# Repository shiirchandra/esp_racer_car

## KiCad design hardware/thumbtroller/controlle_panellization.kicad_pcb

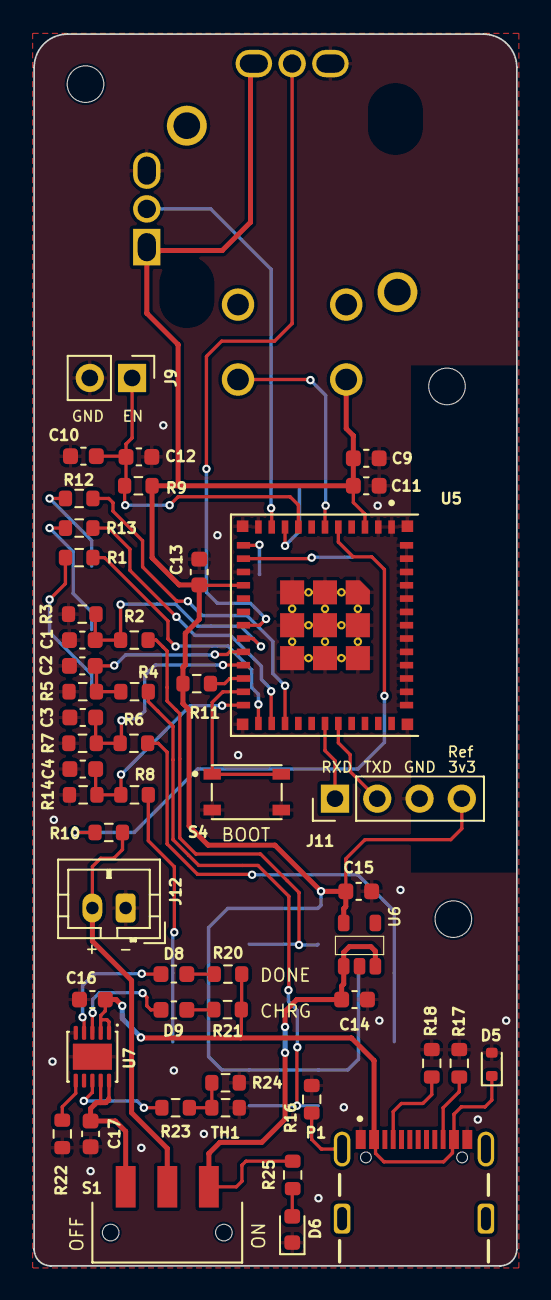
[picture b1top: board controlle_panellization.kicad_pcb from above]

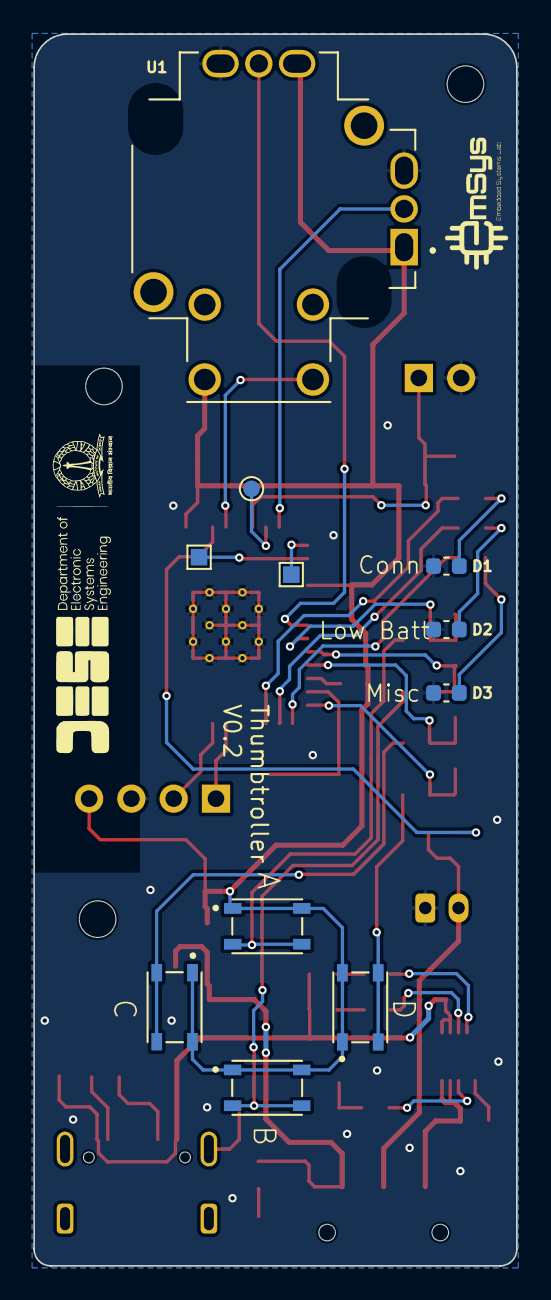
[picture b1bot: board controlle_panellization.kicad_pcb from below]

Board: 4 copper layers, 29.0 x 74.0 mm, 61 parts (11 on the bottom side), 43 nets.

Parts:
C1, C2, C3, C4, C10: 1uF 25V; C_0603_1608Metric
C9: 47uF; C_0603_1608Metric
C11, C12, C13: 0.1uF; C_0603_1608Metric
C14: 2.2uF; C_0603_1608Metric
C15, C16: 10uF; C_0603_1608Metric
C17: 22uF; C_0603_1608Metric
D1, D2, D3, D8, D9: LED; C_0603_1608Metric
D5: TPD1E10B06DPYR; D_SOD-523
D6: PWLED; D_0603_1608Metric
J9: Chip Enable; PinHeader_1x02_P2.54mm_Vertical
J11: UART; PinHeader_1x04_P2.54mm_Vertical
J12: JST 2.0 BATT; JST_PH_B2B-PH-K_1x02_P2.00mm_Vertical
P1: USB_C_Plug_USB2.0; GCT_USB4105-GF-A
R1, R12, R13, R25: 200; R_0603_1608Metric
R2, R4, R6, R8, R9, R10, R11: 10k; R_0603_1608Metric
R3, R5, R7, R14: 100k; R_0603_1608Metric
R16: 1M; R_0603_1608Metric
R17, R18: 5k1; R_0603_1608Metric
R20, R21: 470; R_0603_1608Metric
R22, R23: 1.43K; R_0603_1608Metric
R24: 75K; R_0603_1608Metric
S1: JS102011SAQN; SW_JS102011SAQN
S2, S3, S4, S5, S6: TL4100AF240QG_; SW_PTS810_SJM_250_SMTR_LFS
TH1: TH 10k; R_0603_1608Metric
TP1: 0_IN1; TestPoint_Pad_1.0x1.0mm
TP2: 0_IN2; TestPoint_Pad_1.0x1.0mm
TP3: TP; TestPoint_Pad_D1.0mm
U1: THB001P; CNK_THB001P
U5: ESP32-H2-MINI-1; MODULE_ESP32-H2-MINI-1-H2
U6: AP2204
U7: MCP73833; SON50P300X300X100-11N

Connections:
+3V3: C9.1, C11.1, C13.1, C15.1, J11.4, R9.1, R11.2, S2.1, S3.1, S5.1, S6.1, U1.C, U1.VR1_1, U1.VR2_1, U5.3 (3v3), U5.15 (VBAT), U6.5 (VOUT)
+5V: C16.1, D5.1, P1.A4 (VBUS), P1.A9 (VBUS), R20.1, R21.1, U7.1 (VDD), U7.2 (VDD)
/ADC_BATT: R10.2, U5.5 (IO2)
/CHRGR+: C17.1, S1.1, U7.9 (VBAT), U7.10 (VBAT)
/CP_EN: C10.1, C12.1, J9.1, R9.2, U5.8 (EN)
/STAT1: D9.1 (K), U7.3 (STAT1)
/STAT2: D8.1 (K), U7.4 (STAT2)
/SW_A: C1.1, R2.1, R3.1, U5.19 (IO5)
/SW_B: C2.1, R4.1, R5.1, U5.20 (IO10)
/SW_C: C3.1, R6.1, R7.1, U5.21 (IO11)
/SW_D: C4.1, R8.1, R14.1, U5.24 (IO22)
/U0RXD: J11.1, U5.30 (RXD0)
/U0TXD: J11.2, U5.31 (TXD0)
/VR1: U1.VR1_2, U5.10 (IO01)
/VR2: U1.VR2_2, U5.18 (IO4)
/VR_BTN: U1.D, U5.6 (IO3)
/raw_voltage: C14.1, R25.2, S1.3, U6.1 (VIN), U6.3 (EN)
GND: C1.2, C2.2, C3.2, C4.2, C9.2, C10.2, C11.2, C12.2, C13.2, C14.2, C15.2, C16.2, C17.2, D1.1 (K), D2.1 (K), D3.1 (K), D5.2, D6.1 (K), J9.2, J11.3, J12.1, P1.A1 (GND), P1.A12 (GND), R3.2, R5.2, R7.2, R14.2, R16.2, R17.2, R18.2, R22.2, R24.1, S4.2, TH1.2, U1.VR1_3, U1.VR2_3, U5.1 (GND), U5.2 (GND), U5.11 (GND), U5.14 (GND), U5.36 (GND), U5.37 (GND), U5.38 (GND), U5.39 (GND), U5.40 (GND), U5.41 (GND), U5.42 (GND), U5.43 (GND), U5.44 (GND), U5.45 (GND), U5.46 (GND), U5.47 (GND), U5.48 (GND), U5.49 (EPAD), U5.50 (GND), U5.51 (GND), U5.52 (GND), U5.53 (GND), U6.2 (GND), U7.5 (VSS), U7.11 (PAD)
LIPO+: J12.2, R10.1, S1.2
unnamed: D1.2 (A), R12.1
unnamed: D2.2 (A), R13.1
unnamed: D3.2 (A), R1.1
unnamed: D6.2 (A), R25.1
unnamed: D8.2 (A), R20.2
unnamed: D9.2 (A), R21.2
unnamed: P1.A5 (CC), R18.1
unnamed: P1.S1 (SHIELD), R16.1
unnamed: P1.B5 (VCONN), R17.1
unnamed: R2.2, S2.2
unnamed: R4.2, S3.2
unnamed: R6.2, S5.2
unnamed: R8.2, S6.2
unnamed: R23.1, R24.2, TH1.1
unnamed: TP3.1, U5.9 (IO0)
unnamed: R11.1, U5.22 (IO08)
unnamed: S4.1, U5.23 (IO9)
unnamed: TP1.1, U5.12 (IO13)
unnamed: TP2.1, U5.13 (IO14)
unnamed: R1.2, U5.25 (IO25)
unnamed: R13.2, U5.26 (IO26)
unnamed: R12.2, U5.27 (IO27)
unnamed: R22.1, U7.6 (PROG)
unnamed: R23.2, U7.8 (THERM)

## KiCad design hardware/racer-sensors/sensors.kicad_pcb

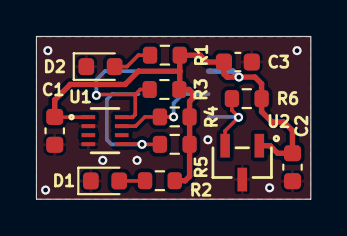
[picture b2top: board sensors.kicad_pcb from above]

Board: 4 copper layers, 15.2 x 9.0 mm, 14 parts (1 on the bottom side), 8 nets.

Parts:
C1, C2: 0.1uF; C_0603_1608Metric
C3: 4.7uF; C_0603_1608Metric
D1, D2: LED; LED_0603_1608Metric
J1: Conn_02x03_SMT; PinHeader_2x03_P1.27mm_Vertical_SMD
R1, R2: 470; R_0603_1608Metric
R3, R4, R5, R6: 10K; R_0603_1608Metric
U1: OPT4060DTSR; FCSOT8_DTS_TEX
U2: HAL1501SU-A; SOT-23_TO-236_TDK

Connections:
+3V3: C1.1, C2.1, C3.1, J1.6, R1.1, R2.1, R3.1, R4.1, R5.1, R6.1, U1.1 (VDD), U2.1 (VSUP)
/HAL_OUT: J1.2, R6.2, U2.2 (OUT)
/OPT_INT: J1.4, R4.2, U1.7 (INT)
/SCL: J1.3, R5.2, U1.5 (SCL)
/SDA: J1.5, R3.2, U1.8 (SDA)
GND: C1.2, C2.2, C3.2, D1.1 (K), D2.1 (K), J1.1, U1.2 (ADDR), U1.4 (GND), U2.3 (GND)
unnamed: D1.2 (A), R2.2
unnamed: D2.2 (A), R1.2

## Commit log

2025-01-25 Intial commit of racer project
